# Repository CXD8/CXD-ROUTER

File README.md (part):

# CXD-ROUTER

CXD-ROUTER is a high-speed, modular router built on a Rockchip RK3588 SoC, powered by USB-C PD.

Goal of Project:
Most consumer routers are locked down and unupgrade. I built this as a high-performance router where networking hardware (e.g., m.2 Wi-Fi modules) can be easily upgraded using M.2 slots without replacing the entire device.

## Specifications and Features

| Component | Details |
| :--- | :--- |
| **SoC** | Rockchip RK3588 |
| **Memory** | Onboard LPDDR4 memory |
| **Storage** | Onboard eMMC storage |
| **Upgradable Modules** | M.2 slots for 2.5GbE Ethernet and BE3600 Wi-Fi cards |
| **Power** | USB-C Power Delivery (PD) 12V |
| **I/O** | Mini HDMI, USB-C, 2.5G RJ45 |

## Firmware, flashing and setup

1. Follow Firefly's or Fygo's existing documentation to flash the RK3588 board (image itself cant be uploaded here due to size; flashing tools included in firmware folder):  
   [Fygo ROC-RK3588-PC Upgrade Firmware Guide](https://help.fygonas.com/articles/v1/contact/arm-rk-usb)  
   [Firefly ROC-RK3588-PC Upgrade Firmware Guide](https://wiki.t-firefly.com/en/ROC-RK3588-PC/upgrade_firmware.html)  
3. Connect peripherals (OPT: M.2 WiFi Card)
4. Plug in your network cable and Mini HDMI to a monitor.
5. Connect a 12v USB-C PD compatible power source to the board.

## Images
 **PCB:**

 **Housing:**

## Bill of Materials
|CXD-ROUTER-V1.0.0.csv|                      |                           |                               | |   |                    |     |          |        |                               | | | |                                                                                                         |                                            |
|---------------------|---------------------------|--------------------------------|------------------------------------|------|--------|-------------------------|----------|---------------|--------------|-------------------------------------|-------|-------|-------|---------------------------------------------------------------------------------------------------------------|--------------------------------------------------|
|                     |                           |                                |                                    |      |        |                         |          |               |              |                                     |       |       |       |                                                                                                               |                                                  |
|                     |                           |                                |                                    |      |        |                         |          |               |              |                                     |       |       |       |                                                                                                               |                                                  |
|Uploaded data        |                           |                                |                                    |      |        |                         |          |               |              |                                     |       |       |       |                                                                                                               |                                                  |
|LCSC#                |Mrf#                       |Description                     |Package                             |Value |Quantity|Mfr.                     |Order Qty.|Unit Price(USD)|Ext.Price(USD)|Package                              |Min    |Mult   |SPQ    |Description                                                                                                    |Product Link                                      |
|C49062               |CL03A104KP3NNNC            |100nF X5R 10V 0201              |CL03A104KP3NNNC                     |      |46      |Samsung Electro-Mechanics|100       |0.0047         |0.47          |0201                                 |100    |100    |10000  |100nF �10% 10V Ceramic Capacitor X5R 0201                                                                      |https://www.lcsc.com/product-detail/C49062.html   |
|C59461               |CL10A226MQ8NRNC            |22uF X5R 6.3V 0603              |CL10A226MQ8NRNC                     |      |26      |Samsung Electro-Mechanics|40        |0.0313         |1.25          |0603                                 |20     |20     |4000   |22uF �20% 6.3V Ceramic Capacitor X5R 0603                                                                      |https://www.lcsc.com/product-detail/C59461.html   |
|C190187              |CC0201KRX5R5BB104          |100nF 6.3V 0201                 |RC0201FR-0749R9L                    |      |16      |YAGEO                    |100       |0.0040         |0.40          |0201                                 |100    |100    |15000  |100nF �10% 6.3V Ceramic Capacitor X5R 0201                                                                     |https://www.lcsc.com/product-detail/C190187.html  |
|C541330              |CC0201KRX5R5BB105          |1uF 6.3V 0201                   |RC0201FR-0749R9L                    |      |15      |YAGEO                    |100       |0.0071         |0.71          |0201                                 |100    |100    |15000  |1uF �10% 6.3V Ceramic Capacitor X5R 0201                                                                       |https://www.lcsc.com/product-detail/C541330.html  |
|C315248              |CL05A106MP5NUNC            |10uF X5R 4V 0402_BGA            |RC0402JR-070RL                      |      |13      |Samsung Electro-Mechanics|20        |0.0516         |1.03          |0402                                 |20     |20     |10000  |10uF �20% 10V Ceramic Capacitor X5R 0402                                                                       |https://www.lcsc.com/product-detail/C315248.html  |
|C3020456             |GRM188R60J226KEA0D         |22uF 0603 6.3V X5R              |GRM188R60J226KEA0D                  |      |12      |muRata                   |20        |0.0488         |0.98          |0603                                 |20     |20     |4000   |22uF �10% 6.3V Ceramic Capacitor X5R 0603                                                                      |https://www.lcsc.com/product-detail/C3020456.html |
|C307380              |CL03A104KO3NNNC            |100nF X5R 16V 0201              |RC0201FR-0749R9L                    |      |11      |Samsung Electro-Mechanics|100       |0.0062         |0.62          |0201                                 |100    |100    |10000  |100nF �10% 16V Ceramic Capacitor X5R 0201                                                                      |https://www.lcsc.com/product-detail/C307380.html  |
|C318688              |CL21A226KPCLRNC            |22uF 10V 0805 10%               |CL21A226KPCLRNC                     |      |11      |Samsung Electro-Mechanics|20        |0.0823         |1.65          |0805                                 |10     |10     |4000   |22uF �10% 10V Ceramic Capacitor X5R 0805                                                                       |https://www.lcsc.com/product-detail/C318688.html  |
|C190187              |CC0201KRX5R5BB104          |100nF 0201 6.3V                 |RC0201FR-0749R9L                    |      |10      |YAGEO                    |100       |0.0040         |0.40          |0201                                 |100    |100    |15000  |100nF �10% 6.3V Ceramic Capacitor X5R 0201                                                                     |https://www.lcsc.com/product-detail/C190187.html  |
|C105882              |CC0402KRX5R9BB104          |100nF 50V 0402                  |RC0402JR-070RL                      |      |10      |YAGEO                    |50        |0.0155         |0.78          |0402                                 |50     |50     |10000  |100nF �10% 50V Ceramic Capacitor X5R 0402                                                                      |https://www.lcsc.com/product-detail/C105882.html  |
|C14445               |CL05A105KP5NNNC            |1uF X5R 10V 0402                |FRC0402F1693TS                      |      |10      |Samsung Electro-Mechanics|50        |0.0128         |0.64          |0402                                 |50     |50     |10000  |1uF �10% 10V Ceramic Capacitor X5R 0402                                                                        |https://www.lcsc.com/product-detail/C14445.html   |
|C19702               |CL10A106KP8NNNC            |10uF X5R 10V 0603               |CL10A106KP8NNNC                     |      |9       |Samsung Electro-Mechanics|20        |0.0391         |0.78          |0603                                 |20     |20     |4000   |10uF �10% 10V Ceramic Capacitor X5R 0603                                                                       |https://www.lcsc.com/product-detail/C19702.html   |
|C107372              |CL05A105KQ5NNNC            |1uF X5R 6.3V 0201               |CL05A105KQ5NNNC                     |      |8       |Samsung Electro-Mechanics|100       |0.0076         |0.76          |0402                                 |100    |100    |10000  |1uF �10% 6.3V Ceramic Capacitor X5R 0402                                                                       |https://www.lcsc.com/product-detail/C107372.html  |
|C49062               |CL03A104KP3NNNC            |100nF X5R 100V 0201             |CL03A104KP3NNNC                     |      |8       |Samsung Electro-Mechanics|100       |0.0047         |0.47          |0201                                 |100    |100    |10000  |100nF �10% 10V Ceramic Capacitor X5R 0201                                                                      |https://www.lcsc.com/product-detail/C49062.html   |
|C3020456             |GRM188R60J226KEA0D         |22uF X5R 6.3V 0603              |GRM188R60J226KEA0D                  |      |8       |muRata                   |20        |0.0488         |0.98          |0603                                 |20     |20     |4000   |22uF �10% 6.3V Ceramic Capacitor X5R 0603                                                                      |https://www.lcsc.com/product-detail/C3020456.html |
|C440198              |GRM21BR61H106KE43L         |10uF 50V 0805                   |GRM21BR61H106KE43L                  |      |8       |muRata                   |10        |0.3246         |3.25          |0805                                 |5      |5      |3000   |10uF �10% 50V Ceramic Capacitor X5R 0805                                                                       |https://www.lcsc.com/product-detail/C440198.html  |
|C49062               |CL03A104KP3NNNC            |100nF 0201 10V X5R              |CL03A104KP3NNNC                     |      |7       |Samsung Electro-Mechanics|100       |0.0047         |0.47          |0201                                 |100    |100    |10000  |100nF �10% 10V Ceramic Capacitor X5R 0201                                                                      |https://www.lcsc.com/product-detail/C49062.html   |
|C170151              |CL05A225KO5NQNC            |16V 2.2uF 0402                  |FRC0402F1693TS                      |      |7       |Samsung Electro-Mechanics|50        |0.0291         |1.46          |0402                                 |50     |50     |10000  |2.2uF �10% 16V Ceramic Capacitor X5R 0402                                                                      |https://www.lcsc.com/product-detail/C170151.html  |
|C161455              |GRM033C80G105MEA2D         |1uF 4V 0201                     |RC0201FR-0749R9L                    |      |6       |muRata                   |20        |0.0279         |0.56          |0201                                 |20     |20     |15000  |1uF �20% 4V Ceramic Capacitor X6S 0201                                                                         |https://www.lcsc.com/product-detail/C161455.html  |
|C541330              |CC0201KRX5R5BB105          |1uF X5R 6.3V 0201               |RC0201FR-0749R9L                    |      |6       |YAGEO                    |100       |0.0071         |0.71          |0201                                 |100    |100    |15000  |1uF �10% 6.3V Ceramic Capacitor X5R 0201                                                                       |https://www.lcsc.com/product-detail/C541330.html  |
|C315248              |CL05A106MP5NUNC            |10V 10uF 0402                   |10uF_X5R_10V_0402                   |      |5       |Samsung Electro-Mechanics|20        |0.0516         |1.03          |0402                                 |20     |20     |10000  |10uF �20% 10V Ceramic Capacitor X5R 0402                                                                       |https://www.lcsc.com/product-detail/C315248.html  |
|C170151              |CL05A225KO5NQNC            |2.2uF X5R 6.3V 0402             |FRC0402F1693TS                      |      |5       |Samsung Electro-Mechanics|50        |0.0291         |1.46          |0402                                 |50     |50     |10000  |2.2uF �10% 16V Ceramic Capacitor X5R 0402                                                                      |https://www.lcsc.com/product-detail/C170151.html  |
|C14445               |CL05A105KP5NNNC            |1uF X5R 6.3V 0402               |FRC0402F1693TS                      |      |5       |Samsung Electro-Mechanics|50        |0.0128         |0.64          |0402                                 |50     |50     |10000  |1uF �10% 10V Ceramic Capacitor X5R 0402                                                                        |https://www.lcsc.com/product-detail/C14445.html   |
|C526941              |CC0201JRX7R8BB102          |1nF 25V X7R 0201                |RC0201FR-0749R9L                    |      |5       |YAGEO                    |100       |0.0052         |0.52          |0201                                 |100    |100    |15000  |1nF �5% 25V Ceramic Capacitor X7R 0201                                                                         |https://www.lcsc.com/product-detail/C526941.html  |
|C368809              |CL05A475KP5NRNC            |4.7uF 10V 04024                 |RC0402JR-070RL                      |      |4       |Samsung Electro-Mechanics|50        |0.0170         |0.85          |0402                                 |50     |50     |10000  |4.7uF �10% 10V Ceramic Capacitor X5R 0402                                                                      |https://www.lcsc.com/product-detail/C368809.html  |
|C190187              |CC0201KRX5R5BB104          |100nF 0201 6.3V X5R             |RC0201FR-0749R9L                    |      |4       |YAGEO                    |100       |0.0040         |0.40          |0201                                 |100    |100    |15000  |100nF �10% 6.3V Ceramic Capacitor X5R 0201                                                                     |https://www.lcsc.com/product-detail/C190187.html  |
|C3845593             |GRM158R61A226ME15D         |22uF X5R 10V                    |RC0402JR-070RL                      |      |4       |muRata                   |4         |0.7950         |3.18          |0402                                 |1      |1      |8000   |22uF �20% 10V Ceramic Capacitor X5R 0402                                                                       |https://www.lcsc.com/product-detail/C3845593.html |
|C105882              |CC0402KRX5R9BB104          |100nF 0402 50V                  |RC0402JR-070RL                      |      |4       |YAGEO                    |50        |0.0155         |0.78          |0402                                 |50     |50     |10000  |100nF �10% 50V Ceramic Capacitor X5R 0402                                                                      |https://www.lcsc.com/product-detail/C105882.html  |
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
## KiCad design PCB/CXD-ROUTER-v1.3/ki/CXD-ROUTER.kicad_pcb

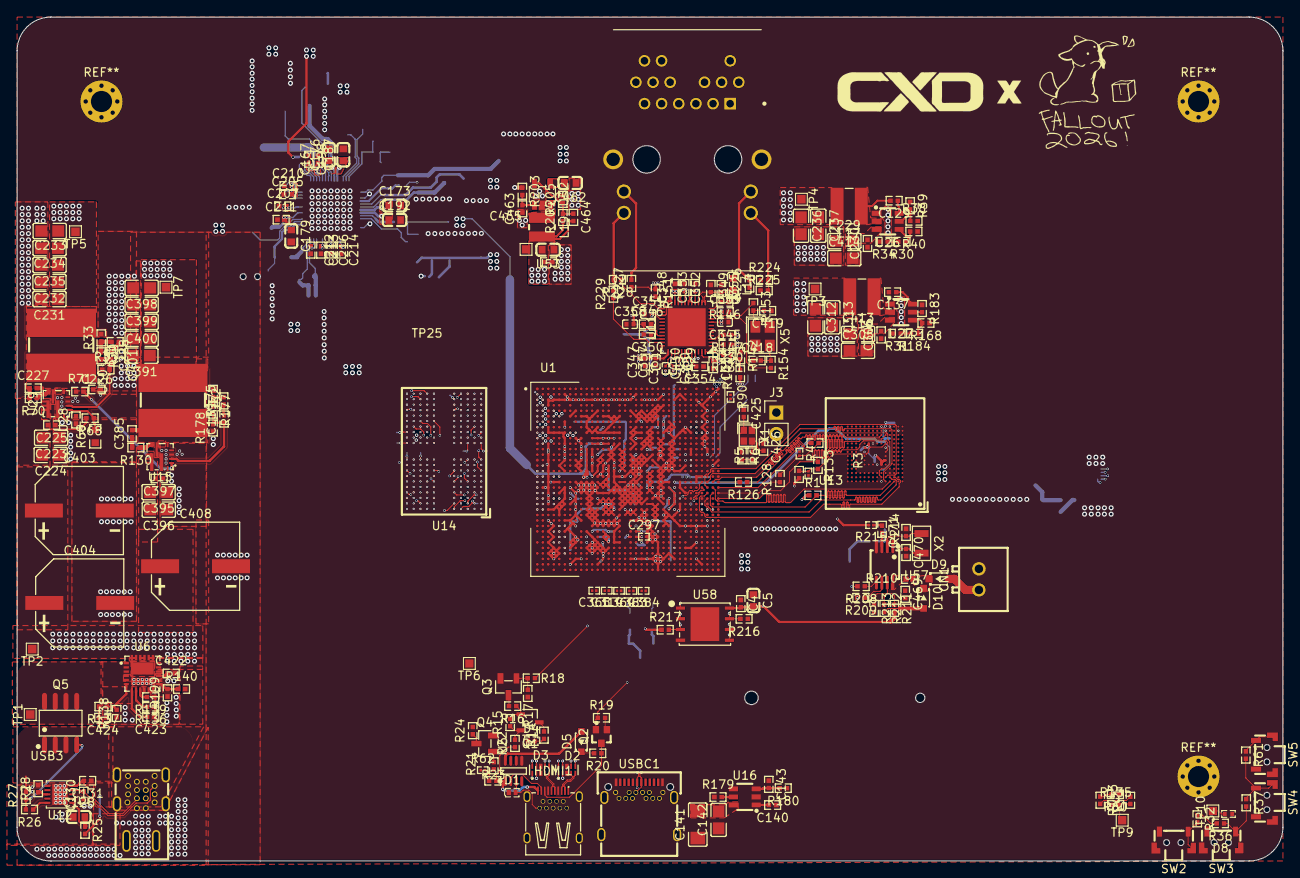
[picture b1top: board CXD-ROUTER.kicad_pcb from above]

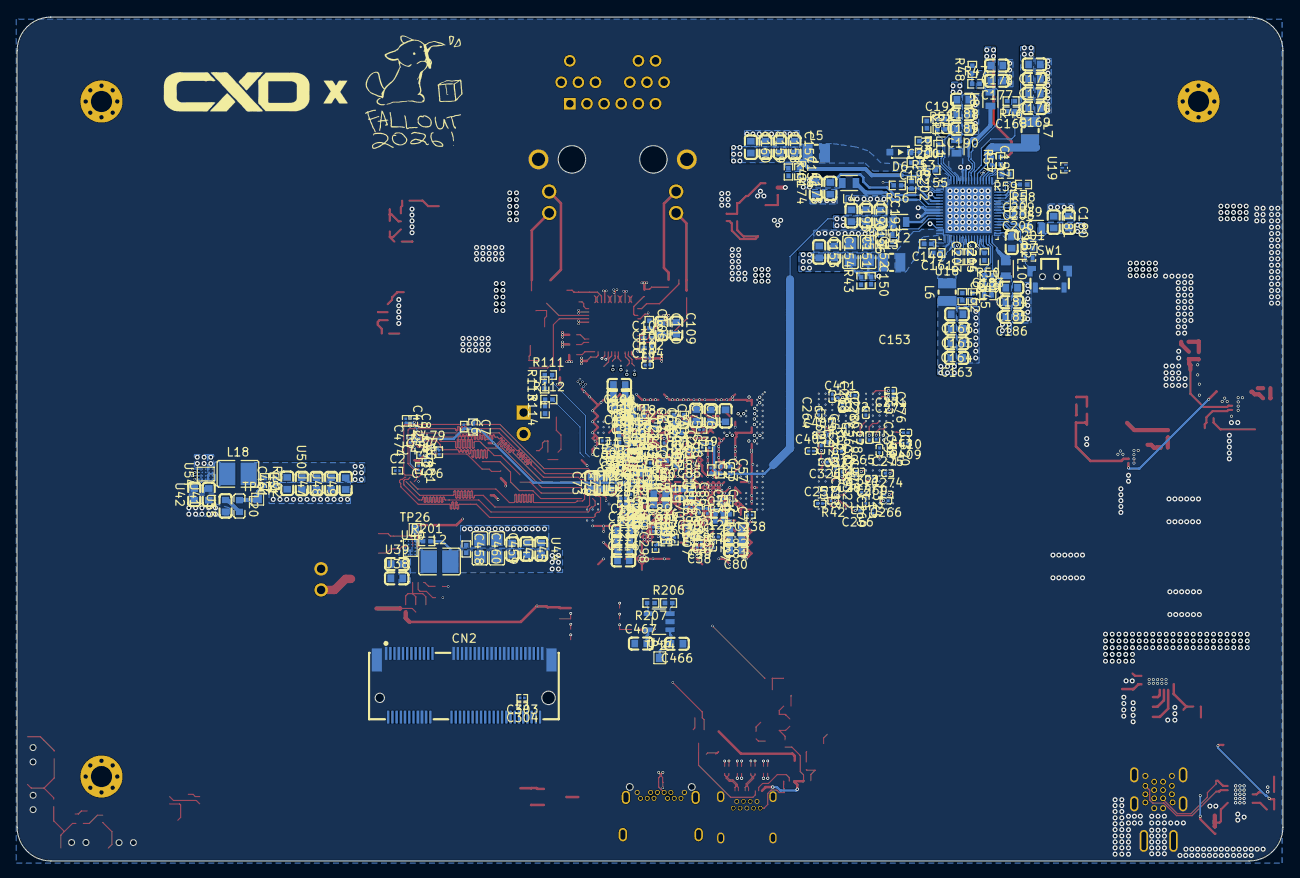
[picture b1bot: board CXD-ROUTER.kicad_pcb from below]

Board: 10 copper layers, 150.0 x 100.0 mm, 552 parts (301 on the bottom side), 311 nets.

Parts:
C1, C2, C3, C6, C8, C11, C12, C13, C14, C15, C17, C18, C20, C22, C24, C26, C28, C29, C30, C32, C33, C34, C35, C36, C37, C38, C39, C46, C47, C48, C49, C50, C51, C58, C63, C64, C70, C102, C112, C238, C281, C282, C286, C287, C288, C289, C290, C291, C292, C293, C295, C296, C297, C298, C303, C304, C307, C314, C364, C365, C383, C384, C439, C472, C474, C475, C476, C477, C478, C479, C481: -; RC0201FR-0749R9L
C4, C7, C19, C21, C23, C25, C27, C54, C55, C56, C65, C66, C67, C71, C72, C79, C87, C88, C96, C97, C98, C106, C107, C108, C113, C129, C130, C131, C137, C139, C140, C143, C149, C155, C161, C167, C225, C226, C227, C228, C230, C306, C349, C355, C385, C397, C424, C463, C465, C469: -; RC0402JR-070RL
C5, C128: -; CL10B105KA8NNNC
C16: -; RC0201FR-0747KL
C43, C150, C156, C162, C168, C183, C191, C196, C198, C199, C200, C201, C202, C203, C204, C205, C206, C207, C208, C209, C210, C211, C212, C213, C214, C215, C216, C346, C347, C348, C350, C352, C353, C354, C356, C359, C458, C461, C464: -; FRC0402F1693TS
C53, C59, C61, C62, C68, C69, C84, C85, C92, C93, C103, C104, C111, C121, C123, C125, C127, C256, C257, C260, C262, C263, C264, C265, C266, C267, C268, C269, C270, C271, C272, C273, C274, C275, C276, C277, C278, C280, C299, C300, C301, C302, C317, C318, C319, C320, C321, C322, C323, C324, C325, C326, C327, C360, C361, C405, C407, C409, C410, C411, C412, C429, C430: -; CL03A104KP3NNNC
C57, C345, C351, C357, C358: -; 10uF_X5R_10V_0402
C60, C86, C94, C95, C119, C120, C197: -; CL05A105KQ5NNNC
C73, C74, C75, C76, C77, C78, C80, C81, C82, C89, C90, C99, C100, C101, C109, C110, C114, C115, C116, C117: -; GRM188R60J226KEA0D
C141: -; GRM31CR61A107MEA8L
C142, C459, C460: -; GRM21BR61A476ME15L
C151, C152: -; CL21A476MQYNNNE
C153, C154, C157, C158, C159, C160, C163, C164, C165, C166, C169, C170, C171, C172, C174, C175, C177, C178, C180, C181, C185, C186, C188, C189, C193, C194: -; CL10A226MQ8NRNC
C173, C176, C179, C182, C184, C187, C190, C192, C195, C462, C466, C467: -; CL10A106KP8NNNC
C223, C224, C229, C305, C395, C396, C413, C414: -; GRM21BR61H106KE43L
C231, C232, C233, C234, C235, C236, C237, C312, C313, C391, C398, C399, C400, C401: -; CL21A226KPCLRNC
C239: -; RC0201FR-07240RL
C403, C404, C408: -; VKME1001K101MV
C418, C419, C422, C423, C425, C426, C470, C471: -; RC0402FR-071KL
CN1: -; B2B-XH-2_LF_SN
CN2: -; 2199230-4_C2977809
D1, D4: -; ESD5341N-2_TR
D2, D3: -; ESD5304D-10_TR
D5, D6, D9, D10: -; B5819WS_C916992
D7, D8: -; ESD5451N-2_TR
HDMI1: -; HDMI-GD-121PWB
J2: -; PULSE_JT4-1108HL
J3: -; PinHeader_1x02_P2.54mm_Vertical
L2, L18: -; FTC322512SR22MBCA
L3, L5, L6, L7: -; APS252012MR22F
L4, L8, L9, L10, L11, L12: -; MTC201208-R47MT
L14: -; BLM18PG330SN1D
L16, L17: -; FTC404030S3R3MGCA
L19: -; FTC303020D2R2MBCA
L20: -; BLM18KG121TN1D
Q1: -; WPM3407-3_TR
Q2: -; 2SK3018T106
Q3, Q4: -; S8050-J3Y_C18221467
Q5: -; AO4407A
R1, R2, R3, R15, R16, R18: -; RC0402JR-0710KL
R4, R62, R215: -; RC0201FR-0747KL
R5: -; CRCW040222R0JNED
R6: -; RC0402FR-07510KL
R14: -; RC0402JR-071KL
R17: -; RC0402JR-0720KL
R19, R40, R56, R57, R66, R178, R203, R207, R211, R216, R217: -; RC0402FR-0710KL
R20: -; RC0402JR-0727KL
R21, R22, R31, R33, R34, R47, R48, R70, R73, R126, R128, R130, R133, R135, R143, R153, R154, R176, R208, R209, R210, R212, R214, R224, R228, R229: -; RC0402JR-070RL
R23, R24, R111, R112: -; RC0402JR-07100KL
R25: -; RC0402FR-0710RL
R26: -; RC0402FR-075K1L
R27: -; RC0402FR-0749K9L
R28: -; 0402WGF1402TCE
R29: -; RC0402FR-0768KL
R30, R199: -; RC0402FR-0733K2L
R32, R201, R202: -; RC0402FR-07100RL
R35, R61: -; RC0402FR-0712KL
R36: -; RC0402FR-073KL
R37: -; RC0402FR-076K8L
R38: -; AF0402FR-07511KL
R39: -; ARG02BTC1053
R41, R43, R44, R45, R46, R49, R51, R55, R58, R59, R60, R71, R140, R168, R180, R183, R204: -; RC0402FR-07100KL
R42: -; RC0201FR-07240RL
R50, R175: -; RC0402FR-0720KL
R52, R113, R114, R138, R205: -; RC0402FR-07120KL
R53, R54: -; RT0402BRD07200KL
R68: -; FRC0402F1693TS
R69: -; RT0603BRD0736K1L
R90: -; RC0201FR-07200KL
R136: -; RC0402FR-07300RL
R137: -; RC0402FR-071ML
R139, R141: -; RC0402FR-071KL
R142: -; RC0402FR-0715KL
R146: -; RC0402FR-072K49L
R147, R151, R206, R230, R231: -; RC0402FR-074K7L
R177: -; RT0402BRD0745K3L
R179: -; AT0402BRD0726K1L
R184: -; RT0402BRD0723K7L
R213: -; RC0402JR-0722RL
R225, R226: -; CRCW0402249RFKED
R227: -; RC0402FR-07510RL
SW1, SW2, SW3, SW4, SW5: -; TS24CA
TP1, TP2, TP3, TP4, TP5, TP6, TP7, TP9, TP10, TP23, TP24, TP25, TP26: -; TestPoint_Pad_1.0x1.0mm
U1: -; BGA1088C65P34X34_2300X2300X204N
U5: -; RS0102YH8
U6: -; TPS259804ONRGER
U11: -; RTL8125BG-CG
U12: -; WDFN-10-1EP_3x3mm_P0.5mm_EP1.8x2.5mm
U13: -; KLMBG2JETD-B041
U14: -; H9HCNNN8KUMLHR-NME
U15: -; TPS56637RPAR
U16: -; TPS2553DBVR
U18: -; QFN35P700X700X90-69N
U19: -; RCLAMP0512TQTCT
U26, U27: -; TPS563201DDCR
U28: -; RT0402BRD0752K3L
U29: -; TPS56A37RPAR
U30, U32: -; FEXL0730A-3R3M
U38, U39, U41, U42, U43, U44, U45, U47, U48, U49, U50, U51, U53, U55: -; GRM188R60J226KEA0D
U40: -; RK860-2
U46: -; SGM2576YN5G_TR
U52: -; SY8089AAAC
U54: -; RK860-3
U57: -; HYM8563S
U58: -; W25Q256JWPIQ
USB3: -; HC-TYPE-C-16P-FL6_65Q-5A-06
USBC1: -; TYPE-C-31-M-04
X1: -; XL7EL89CKI-111YLC-24M
X2: -; SC-32S32_768kHz20PPM12_5pF
X5: -; XL2EL89COI-111YLC-25M

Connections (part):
0V95_ETH: C312.1, C313.1, C345.2, C347.2, C348.1, C351.2, C353.1, C356.1, C357.2, C359.1, L16.2, R31.2, TP3.1 (1_1), U11.8 (DVDD09), U11.11 (AVDD09), U11.16 (AVDD09), U11.22 (AVDD09), U11.28 (DVDD09), U11.37 (EVDD09), U11.47 (DVDD09)
3V3_M0: C391.1, C398.1, C399.1, C400.1, C401.1, CN2.2 (3.3V), CN2.4 (3.3V), CN2.72 (3.3V), CN2.74 (3.3V), R176.2, TP7.1 (1_1), U32.2
/5V_USB_1: C141.2, C142.2, U16.6 (OUT), USBC1.A4 (VBUS), USBC1.A9 (VBUS), USBC1.B4 (VBUS), USBC1.B9 (VBUS)
/15V_PD_OUT: C223.2, C224.2, C225.2, C229.2, C230.2, C395.2, C396.2, C397.2, C403.1, C404.1, C408.1, C414.2, R38.2, R68.2, R140.2, TP2.1 (1_1), U6.17 (OUT), U6.18 (OUT), U6.19 (OUT), U6.20 (OUT), U6.21 (OUT), U6.22 (OUT), U6.23 (OUT), U6.24 (OUT), U15.8 (VIN), U26.3 (VIN), U29.8 (VIN)
/15V_PD_OUT_UNFUSED: C424.2, Q5.5 (D), Q5.6 (D), Q5.7 (D), Q5.8 (D), R137.2, TP1.1 (1_1), U6.1 (IN), U6.2 (IN), U6.3 (IN), U6.16 (IN), U6.25 (IN)
/ETHERNET & MAGNETICS/AVDD33_PLL_E2: C349.2, C355.2, L14.2, U11.15 (AVDD33)
/ETHERNET & MAGNETICS/CKXTAL1_E2: R153.1, U11.10 (CKXTAL1)
/ETHERNET & MAGNETICS/CKXTAL2_E2: R154.2, U11.9 (CKXTAL2)
/ETHERNET & MAGNETICS/CLKREQB_E2: R231.2, U11.48 (CLKREQB)
/ETHERNET & MAGNETICS/DVDD33_29_E2: U11.29 (DVDD33), U11.46 (DVDD33)
/ETHERNET & MAGNETICS/EVDD33_E0: C354.2, J2.1 (TRCT2), J2.6 (TRCT3), J2.7 (TRCT1), J2.12 (TRCT4), U11.43 (EVDD33)
/ETHERNET & MAGNETICS/GIP/GPO_E2: R147.2, U11.3 (GPI)
/ETHERNET & MAGNETICS/LANWAKEB_E2: R230.2, U11.2 (LANWAKEB)
/ETHERNET & MAGNETICS/LED0/EEDI/SPISI/SDA_E2: R225.1, U11.30 (LED0/EEDI/SPISI/SDA)
/ETHERNET & MAGNETICS/LED1/EESK/SPISCK_E2: R151.2, R226.1, U11.27 (LED1/EESK/SPISC)
/ETHERNET & MAGNETICS/LED2/EEDO/SPISO_E2: R228.1, U11.25 (LED2/EEDO/SPIS0)
/ETHERNET & MAGNETICS/LED3_E2: R229.1, U11.35 (LED3)
/ETHERNET & MAGNETICS/MDIN0_2: J2.9 (TRD1-), U11.14 (MDIN0)
/ETHERNET & MAGNETICS/MDIN1_2: J2.3 (TRD2-), U11.18 (MDIN1)
/ETHERNET & MAGNETICS/MDIN2_2: J2.5 (TRD3-), U11.21 (MDIN2)
/ETHERNET & MAGNETICS/MDIN3_2: J2.11 (TRD4-), U11.24 (MDIN3)
/ETHERNET & MAGNETICS/MDIP0_2: J2.8 (TRD1+), U11.13 (MDIP0)
/ETHERNET & MAGNETICS/MDIP1_2: J2.2 (TRD2+), U11.17 (MDIP1)
/ETHERNET & MAGNETICS/MDIP2_2: J2.4 (TRD3+), U11.20 (MDIP2)
/ETHERNET & MAGNETICS/MDIP3_2: J2.10 (TRD4+), U11.23 (MDIP3)
/ETHERNET & MAGNETICS/RSET_E2: R146.2, U11.12 (RSET)
/HDMIIRX_DET_L: Q4.3 (C), R24.1
/HDMI_RXDDC_SCL_PORT: HDMI1.17 (SCL), U5.2 (B1)
/HDMI_RXDDC_SDA_PORT: D1.2, HDMI1.18 (SDA), U5.3 (B2)
/MIPI DSI & CSI INTERFACES - Q | R | P/PCIE30_0_REF: R90.1, U1.B34 (PCIE30_PORT0_RESREF)
/PMIC RK806-1/PMIC_FB6: C191.1, R51.2, R52.1, U18.31 (FB6)
/PMIC RK806-1/PMIC_FB9: C183.1, R49.2, R50.1, U18.66 (FB9)
/PMIC RK806-1/PMIC_SW1: L3.1, U18.50 (SW1_2), U18.51 (SW1_1)
/PMIC RK806-1/PMIC_SW2: L5.1, U18.35 (SW2), U18.36 (SW2)
/PMIC RK806-1/PMIC_SW3: L6.1, U18.55 (SW3)
/PMIC RK806-1/PMIC_SW4: L7.1, U18.23 (SW4)
/PMIC RK806-1/PMIC_SW5: L12.1, U18.45 (SW5)
/PMIC RK806-1/PMIC_SW6: L11.1, U18.29 (SW6)
/PMIC RK806-1/PMIC_SW9: L10.1, U18.68 (SW9)
/PMIC RK806-1/PMIC_SW10: L8.1, L9.1, U18.6 (SW8), U18.26 (SW10)
/PMIC RK806-1/PMIC_VDC: C200.1, R53.1, R54.1, U18.32 (VDC)
/PMU & CLOCK - E | F/XIN_24M: C425.2, R6.1, U1.R34 (XIN_24M), X1.1
/PMU & CLOCK - E | F/XOUT_24M: R5.1, R6.2, U1.T34 (XOUT_24M)
/TYPEC_VBUS: Q5.1 (S), Q5.2 (S), Q5.3 (S), R25.2, R27.2, USB3.A4 (VBUS), USB3.A9 (VBUS), USB3.B4 (VBUS), USB3.B9 (VBUS)
/VCCIO - J | K | I/VSEL4: R111.2, U1.T32 (PMIC_SLEEP4/GPIO0_C2_D)
/VCCIO - J | K | I/VSEL5: R112.2, U1.T30 (PMIC_SLEEP5/GPIO0_C3_D)
BIG/NPU_EN: U40.A2 (EN), U54.A2 (EN)
BOOT_SARADC_IN0: C314.2, R41.1, R135.2, TP9.1 (1_1), U1.AM16 (SARADC_IN0_BOOT)
CPU_BIG1_VSEL: U1.W28 (PMIC_SLEEP6/PDM0_SDI3_M1/GPIO0_D6_D), U54.A1 (VSEL)
DDR_CH0_A0_A: U1.T7 (DDR_CH0_A0_A), U14.H2 (CA0a)
DDR_CH0_A0_B: U1.M8 (DDR_CH0_A0_B), U14.R2 (CA0b)
DDR_CH0_A1_A: U1.T8 (DDR_CH0_A1_A), U14.J2 (CA1a)
DDR_CH0_A1_B: U1.M5 (DDR_CH0_A1_B), U14.P2 (CA1b)
DDR_CH0_A2_A: U1.P4 (DDR_CH0_A2_A), U14.H9 (CA2a)
DDR_CH0_A2_B: U1.N5 (DDR_CH0_A2_B), U14.R9 (CA2b)
DDR_CH0_A3_A: U1.P5 (DDR_CH0_A3_A), U14.H10 (CA3a)
DDR_CH0_A3_B: U1.N4 (DDR_CH0_A3_B), U14.R10 (CA3b)
DDR_CH0_A4_A: U1.R1 (DDR_CH0_A4_A), U14.H11 (CA4a)
DDR_CH0_A4_B: U1.K1 (DDR_CH0_A4_B), U14.R11 (CA4b)
DDR_CH0_A5_A: U1.P2 (DDR_CH0_A5_A), U14.J11 (CA5a)
DDR_CH0_A5_B: U1.L2 (DDR_CH0_A5_B), U14.P11 (CA5b)
DDR_CH0_CLKN_A: U1.N1 (DDR_CH0_CKB_A), U14.J9 (CK_ca)
DDR_CH0_CLKN_B: U1.M1 (DDR_CH0_CKB_B), U14.P9 (CK_cb)
DDR_CH0_CLKP_A: U1.N2 (DDR_CH0_CK_A), U14.J8 (CK_ta)
DDR_CH0_CLKP_B: U1.M2 (DDR_CH0_CK_B), U14.P8 (CK_tb)
DDR_CH0_DM0_A: U1.Y4 (DDR_CH0_DM0_A), U14.C3 (DMI0a)
DDR_CH0_DM0_B: U1.G4 (DDR_CH0_DM0_B), U14.Y3 (DMI0b)
DDR_CH0_DM1_A: U1.AB4 (DDR_CH0_DM1_A), U14.C10 (DMI1a)
DDR_CH0_DM1_B: U1.E4 (DDR_CH0_DM1_B), U14.Y10 (DMI1b)
DDR_CH0_DQ0_A: U1.U1 (DDR_CH0_DQ0_A), U14.B2 (DQ0a)
DDR_CH0_DQ0_B: U1.H1 (DDR_CH0_DQ0_B), U14.AA2 (DQ0b)
DDR_CH0_DQ1_A: U1.T2 (DDR_CH0_DQ1_A), U14.C2 (DQ1a)
DDR_CH0_DQ1_B: U1.J2 (DDR_CH0_DQ1_B), U14.Y2 (DQ1b)
DDR_CH0_DQ2_A: U1.T1 (DDR_CH0_DQ2_A), U14.E2 (DQ2a)
DDR_CH0_DQ2_B: U1.J1 (DDR_CH0_DQ2_B), U14.V2 (DQ2b)
DDR_CH0_DQ3_A: U1.R2 (DDR_CH0_DQ3_A), U14.F2 (DQ3a)
DDR_CH0_DQ3_B: U1.K2 (DDR_CH0_DQ3_B), U14.U2 (DQ3b)
DDR_CH0_DQ4_A: U1.W1 (DDR_CH0_DQ4_A), U14.F4 (DQ4a)
DDR_CH0_DQ4_B: U1.F1 (DDR_CH0_DQ4_B), U14.U4 (DQ4b)
DDR_CH0_DQ5_A: U1.V2 (DDR_CH0_DQ5_A), U14.E4 (DQ5a)
DDR_CH0_DQ5_B: U1.G2 (DDR_CH0_DQ5_B), U14.V4 (DQ5b)
DDR_CH0_DQ6_A: U1.V1 (DDR_CH0_DQ6_A), U14.C4 (DQ6a)
DDR_CH0_DQ6_B: U1.G1 (DDR_CH0_DQ6_B), U14.Y4 (DQ6b)
DDR_CH0_DQ7_A: U1.U2 (DDR_CH0_DQ7_A), U14.B4 (DQ7a)
DDR_CH0_DQ7_B: U1.H2 (DDR_CH0_DQ7_B), U14.AA4 (DQ7b)
DDR_CH0_DQ8_A: U1.AB2 (DDR_CH0_DQ8_A), U14.B11 (DQ8a)
DDR_CH0_DQ8_B: U1.D2 (DDR_CH0_DQ8_B), U14.AA11 (DQ8b)
DDR_CH0_DQ9_A: U1.AB1 (DDR_CH0_DQ9_A), U14.C11 (DQ9a)
DDR_CH0_DQ9_B: U1.C1 (DDR_CH0_DQ9_B), U14.Y11 (DQ9b)
DDR_CH0_DQ10_A: U1.AC1 (DDR_CH0_DQ10_A), U14.E11 (DQ10a)
DDR_CH0_DQ10_B: U1.C2 (DDR_CH0_DQ10_B), U14.V11 (DQ10b)
DDR_CH0_DQ11_A: U1.AC2 (DDR_CH0_DQ11_A), U14.F11 (DQ11a)
DDR_CH0_DQ11_B: U1.B1 (DDR_CH0_DQ11_B), U14.U11 (DQ11b)
DDR_CH0_DQ12_A: U1.Y1 (DDR_CH0_DQ12_A), U14.F9 (DQ12a)
DDR_CH0_DQ12_B: U1.F2 (DDR_CH0_DQ12_B), U14.U9 (DQ12b)
DDR_CH0_DQ13_A: U1.Y2 (DDR_CH0_DQ13_A), U14.E9 (DQ13a)
DDR_CH0_DQ13_B: U1.E1 (DDR_CH0_DQ13_B), U14.V9 (DQ13b)
DDR_CH0_DQ14_A: U1.AA1 (DDR_CH0_DQ14_A), U14.C9 (DQ14a)
DDR_CH0_DQ14_B: U1.E2 (DDR_CH0_DQ14_B), U14.Y9 (DQ14b)
DDR_CH0_DQ15_A: U1.AA2 (DDR_CH0_DQ15_A), U14.B9 (DQ15a)
DDR_CH0_DQ15_B: U1.D1 (DDR_CH0_DQ15_B), U14.AA9 (DQ15b)
DDR_CH0_DQS0_A_N: U1.U4 (DDR_CH0_DQS0N_A), U14.E3 (DQS0_ca)
DDR_CH0_DQS0_A_P: U1.U5 (DDR_CH0_DQS0P_A), U14.D3 (DQS0_ta)
DDR_CH0_DQS0_B_N: U1.J7 (DDR_CH0_DQS0N_B), U14.V3 (DQS0_cb)
DDR_CH0_DQS0_B_P: U1.J8 (DDR_CH0_DQS0P_B), U14.W3 (DQS0_tb)
DDR_CH0_DQS1_A_N: U1.AA4 (DDR_CH0_DQS1N_A), U14.E10 (DQS1_ca)
DDR_CH0_DQS1_A_P: U1.AA5 (DDR_CH0_DQS1P_A), U14.D10 (DQS1_ta)
DDR_CH0_DQS1_B_N: U1.F4 (DDR_CH0_DQS1N_B), U14.V10 (DQS1_cb)
DDR_CH0_DQS1_B_P: U1.F5 (DDR_CH0_DQS1P_B), U14.W10 (DQS1_tb)
DDR_CH0_LP4/4X_CS0_A: U1.R6 (DDR_CH0_LP4/4X_CS0_A), U14.H4 (CS0a)
DDR_CH0_LP4/4X_CS0_B: U1.L7 (DDR_CH0_LP4/4X_CS0_B), U14.R4 (CS0b)
DDR_CH1_LP4/4X_CKE0_C: U1.D16 (DDR_CH1_LP4/4X_CKE0/LP5_CS0_D), U1.E19 (DDR_CH1_LP4/4X_CS0_D)
DDR_CH1_LP4/4X_CKE1_C: U1.D19 (DDR_CH1_LP4/4X_CS1_D), U1.E16 (DDR_CH1_LP4/4X_CKE1/LP5_CS1_D)
DDR_RESET: C239.1, U1.T4 (DDR_CH0_RESET_A), U14.T11 (RESET)
FSPI_CLK: U1.AE33 (GMAC0_TXCLK/SDIO_CLK_M0/FSPI_CLK_M1/I2C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), U58.6 (CLK)
FSPI_CS0: U1.AB31 (GMAC0_PTP_REFCLK/FSPI_CS0N_M1/HDMI_TX1_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), U58.1 (CS#)
FSPI_D0: U1.AC32 (GMAC0_RXD2/SDIO_D0_M0/FSPI_D0_M1/UART6_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), U58.5 (DI(IO0))
FSPI_D1: U1.AC31 (GMAC0_RXD3/SDIO_D1_M0/FSPI_D1_M1/UART6_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), U58.2 (DO(IO1))
FSPI_D2: R217.2, U1.AE32 (GMAC0_RXCLK/SDIO_D2_M0/FSPI_D2_M1/I2C8_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), U58.3 (WP#(IO2))
FSPI_D3: R216.2, U1.AC33 (GMAC0_TXD2/SDIO_D3_M0/FSPI_D3_M1/I2C8_S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), U58.7 (HOLD#orRESET#(IO3))
GND: C1.1, C2.1, C3.2, C4.1, C5.1, C6.1, C7.1, C8.1, C11.2, C12.2, C13.1, C14.2, C15.2, C16.2, C17.2, C18.2, C19.2, C20.2, C21.2, C22.2, C23.2, C24.2, C25.2, C26.2, C27.2, C28.2, C29.2, C30.2, C32.1, C33.1, C34.1, C35.1, C36.1, C37.1, C38.1, C39.1, C43.1, C46.2, C47.2, C48.2, C49.2, C50.2, C51.2, C53.1, C54.1, C55.1, C56.1, C57.1, C58.1, C59.1, C60.2, C61.2, C62.2, C63.2, C64.2, C65.2, C66.2, C67.2, C68.1, C69.1, C70.1, C71.1, C72.1, C73.1, C74.2, C75.2, C76.2, C77.1, C78.1, C79.1, C80.1, C81.1, C82.1, C84.1, C85.1, C86.2, C87.2, C88.2, C89.2, C90.2, C92.2, C93.2, C94.1, C95.1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
HDMIIRX_HPDOUT_H: R18.2, U1.AA27 (HDMI_TX0_HPD_M1/PCIE30X2_PERSTN_M2/HDMI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)
HDMI_RX_CEC: Q2.1 (S), R19.1, U1.AG23 (CIF_D13/PCIE20X1_2_PERSTN_M0/HDMI_RX_CE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)
HDMI_RX_CEC_PORT: HDMI1.15 (CEC), Q2.3 (D), R20.1
HDMI_RX_CLK_PORT_N: D3.1, D3.10, HDMI1.14 (TMDS_CLOCK-), U1.AF5 (HDMI_RX_CLKN)
HDMI_RX_CLK_PORT_P: D3.2, D3.9, HDMI1.12 (TMDS_CLOCK+), U1.AF6 (HDMI_RX_CLKP)
HDMI_RX_D0_PORT_N: D3.4, D3.7, HDMI1.11 (TMDS_DATA0-), U1.AG4 (HDMI_RX_D0N)
HDMI_RX_D0_PORT_P: D3.5, D3.6, HDMI1.9 (TMDS_DATA0+), U1.AG5 (HDMI_RX_D0P)
HDMI_RX_D1_PORT_N: D2.1, D2.10, HDMI1.8 (TMDS_DATA1-), U1.AH5 (HDMI_RX_D1N)
HDMI_RX_D1_PORT_P: D2.2, D2.9, HDMI1.6 (TMDS_DATA1+), U1.AH6 (HDMI_RX_D1P)
HDMI_RX_D2_PORT_N: D2.4, D2.7, HDMI1.5 (TMDS_DATA2-), U1.AJ4 (HDMI_RX_D2N)
HDMI_RX_D2_PORT_P: D2.5, D2.6, HDMI1.3 (TMDS_DATA2+), U1.AJ5 (HDMI_RX_D2P)
I2C0_SCL_M2: U1.W30 (I2S1_SDO0_M1/CPU_BIG0_AVS/I2C0_SCL_M2/U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), U54.A3 (SCL)
I2C0_SDA_M2: U1.W29 (I2S1_SDO1_M1/I2C0_SDA_M2/UART1_RX_M2/HD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), U54.B1 (SDA)
I2C1_SDA_M2: U1.V28 (I2S1_SDO3_M1/CPU_BIG1_AVS/I2C1_SDA_M2/C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), U40.B1 (SDA)
I2C6_SCL_M0: R209.2, U1.W31 (I2S1_SDI3_M1/PDM0_SDI1_M1/I2C6_SCL_M0/U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)
I2C6_SDA_M0: R208.2, U1.V31 (I2S1_SDI2_M1/PDM0_SDI0_M1/I2C6_SDA_M0/U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)
NPU_VSEL: U1.U32 (PMIC_SLEEP3/GPIO0_C1_D), U40.A1 (VSEL)
unnamed: C139.2, R175.1
unnamed: C227.1, R70.2
unnamed: C228.1, R73.1
unnamed: C385.1, R130.2
unnamed: C418.2, R154.1, X5.3
unnamed: C419.2, R153.2, X5.1
unnamed: C426.2, R5.2, X1.3
unnamed: CN1.1 (POS), D9.2 (A)
unnamed: C304.2, CN2.37 (TX-N)
unnamed: C303.2, CN2.35 (TX-P)
unnamed: D4.2, R14.1
unnamed: D5.1 (K), R20.2
unnamed: C199.1, D6.1 (K), R53.2
unnamed: J2.17 (LEDG1+), R224.2, R225.2
unnamed: J2.16 (LEDG1-), R226.2
unnamed: J2.19 (LEDY+), R228.2, R229.2
unnamed: J2.18 (LEDY-), R227.2
unnamed: L2.1, U40.D3 (LX), U40.D4 (LX), U40.E3 (LX), U40.E4 (LX)
unnamed: L18.1, U54.D3 (LX), U54.D4 (LX), U54.E3 (LX), U54.E4 (LX)
unnamed: Q1.3 (D), R14.2
unnamed: Q1.1 (G), R15.2, R16.1
unnamed: Q1.2 (S), R15.1, R22.2
unnamed: Q3.1 (B), R17.1, R18.1
unnamed: Q3.3 (C), R16.2
unnamed: Q4.1 (B), R21.2
unnamed: Q5.4 (G), R26.2, R27.1
unnamed: R21.1, R23.1, R62.2
unnamed: R29.1, R33.1, R73.2
unnamed: R30.2, R34.1
unnamed: R32.2, SW2.1, SW2.4
unnamed: R36.1, R37.2, SW3.1, SW3.4
unnamed: R37.1, R61.2, SW4.1, SW4.4
unnamed: R61.1, SW5.1, SW5.4
unnamed: R175.2, R176.1, R177.1
unnamed: R31.1, R184.2
unnamed: R126.2, U1.V34 (EMMC_CLKOUT/GPIO2_A1_D)
unnamed: R128.2, U1.Y34 (EMMC_DATA_STROBE/I2C2_SDA_M2/UART5_CTSN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)
unnamed: R133.2, U1.AA34 (EMMC_RSTN/I2C2_SCL_M2/UART5_RTSN_M1/GPI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)
unnamed: C16.1, U1.AF19 (MIPI_D/C_PHY1_VREG)
unnamed: R137.1, R138.2, U6.6 (EN/UVLO)
unnamed: R136.2, U6.8 (ILIM)
unnamed: R139.2, U6.9 (IMON)
unnamed: C423.2, U6.7 (ITIMER)
unnamed: R140.1, R199.2, U6.13 (PG)
unnamed: C422.1, U6.15 (dVdt)
unnamed: R141.2, R142.2, U11.1 (ISOLATEB)
unnamed: C130.2, U12.4 (CC1), USB3.A5 (CC1)
unnamed: C131.2, U12.5 (CC2), USB3.B5 (CC2)
unnamed: R26.1, U12.10 (GATE)
unnamed: C128.2, R25.1, U12.1 (VIN)
unnamed: R28.1, U12.8 (VSET)
unnamed: C2.2, U13.C2 (VDDI)
unnamed: R66.1, U14.T2 (ODTb)
unnamed: R42.1, U14.A5 (ZQ0)
unnamed: R130.1, U15.7 (BOOT)
unnamed: C139.1, R177.2, R178.2, U15.2 (FB)
unnamed: C385.2, U15.6 (SW), U32.1
unnamed: C143.2, R180.2 (2_2), U16.3 (EN), U16.4 (/FAULT)
unnamed: R179.2, U16.5 (ILIM)
unnamed: L4.1, U18.42 (SW7)
unnamed: R38.1, R39.2, U26.5 (EN)
unnamed: C129.2, L17.1, U26.2 (SW)
unnamed: C129.1, U26.6 (VBST)
unnamed: R30.1, R40.2, U26.4 (VFB)
unnamed: C137.2, L16.1, U27.2 (SW)
unnamed: C137.1, U27.6 (VBST)
unnamed: R168.2, R184.1, U27.4 (VFB)
unnamed: R70.1, U29.7 (BOOT)
unnamed: R68.1, R69.2, U29.1 (EN)
unnamed: C228.2, R29.2, R35.2, U29.2 (FB)
unnamed: U28.2, U29.10 (MODE)
unnamed: R71.1, U29.4 (PG)
unnamed: C226.1, U29.5 (SS)
unnamed: C227.2, U29.6 (SW), U30.1
unnamed: R207.2, U46.4 (EN)
unnamed: R206.2, U46.3 (ILIM/OCB)
unnamed: C463.2, R203.2, U52.1 (EN)
unnamed: C464.1, R204.2, R205.1, U52.5 (FB)
unnamed: L19.1, U52.3 (LX)
unnamed: R211.1, R212.1, R213.1, U57.7 (CLKOUT)
unnamed: R214.2, U57.3 (INT#)
unnamed: C470.1, U57.1 (OSCI), X2.2
unnamed: C471.1, U57.2 (OSCO), X2.1
unnamed: R209.1, U57.6 (SCL)
unnamed: R208.1, U57.5 (SDA)
unnamed: C469.1, R210.1, U57.8 (VDD)
PCIE20_1_2_WAKEn_M1_L: U1.AG24 (CIF_D15/PCIE30X2_WAKEN_M2/HDMI_RX_SDA_M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), U1.AH24 (CIF_D12/PCIE20X1_2_WAKEN_M0/HDMI_TX0_SD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)
PCIE20_2_REFCLKN: U1.G30 (PCIE20_2_REFCLKN), U11.45 (REFCLK_N)
PCIE20_2_REFCLKP: U1.G31 (PCIE20_2_REFCLKP), U11.44 (REFCLK_P)
PCIE20_2_RXN: C360.1, C360.2, U1.J30 (PCIE20_2_RXN/SATA30_2_RXN/USB30_2_SSRXN), U11.39 (HSON)
PCIE20_2_RXP: C361.1, C361.2, U1.J31 (PCIE20_2_RXP/SATA30_2_RXP/USB30_2_SSRXP), U11.38 (HSOP)
PCIE20_2_TXN: C430.1, C430.2, U1.H29 (PCIE20_2_TXN/SATA30_2_TXN/USB30_2_SSTXN), U11.42 (HSIN)
PCIE20_2_TXP: C429.1, C429.2, U1.H30 (PCIE20_2_TXP/SATA30_2_TXP/USB30_2_SSTXP), U11.41 (HSIP)
PCIE30_PORT0_RX0N: CN2.43 (RX-N), U1.G34 (PCIE30_PORT0_RX0N)
PCIE30_PORT0_RX0P: CN2.41 (RX-P), U1.G33 (PCIE30_PORT0_RX0P)
PCIE30_PORT0_TX0N: C304.1, U1.D33 (PCIE30_PORT0_TX0N)
PCIE30_PORT0_TX0P: C303.1, U1.D32 (PCIE30_PORT0_TX0P)
PCIE30x1_0_CLKREQn_M1_L: CN2.53 (CLKREQ0), U1.AL29 (CIF_D3/BT1120_D3/PCIE30X1_0_CLKREQN_M1/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)
PCIE30x1_0_PERSTn_M1_L: CN2.52 (PERSTO), U1.AK27 (CIF_D5/BT1120_D5/I2S1_SDI0_M0/PCIE30X1_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)
PCIE30x1_0_WAKEn_M1_L: CN2.55 (PEWAKE0), U1.AL28 (CIF_D4/BT1120_D4/PCIE30X1_0_WAKEN_M1/I2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)
PCIE30x2_PERSTn_M1_L: U1.AK26 (CIF_CLKIN/BT1120_CLKOUT/I2S1_SDI3_M0/PC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), U11.36 (PERSTB)
PMIC_EXT_EN_OUT: R203.1, U18.39 (EXT_EN)
PMIC_INT_L: R57.1, U1.M30 (PMIC_INT_L/GPIO0_A7_U), U18.19 (INT)
PMIC_PWR_CTRL2: R112.1, R114.2, U18.61 (PWRCRTL2)
PMIC_PWR_CTRL3: R111.1, R113.2, U18.16 (MISO/PWRCRTL3)
PMIC_SPI_CS: R59.2, U1.K29 (CLK32K_IN/CLK32K_OUT0/GPIO0_B2__U), U1.K30 (SPI2_CS0_M2/I2C1_SDA_M1/PWM5_M0/UART0_T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), U18.18 (CS)
PMIC_SPI_MOSI: R58.2, U1.L29 (SPI2_MISO_M2/I2C0_SCL_M0/GPIO0_B3_Z), U18.15 (MOSI/SDA)
POW_EXT_SWR: R183.2, U27.5 (EN)
PWRON_L: C201.1, D7.1 (C), SW1.4, U18.4 (PWRON)
RESET_L: C202.2, R56.1, U1.M31 (NPOR), U18.40 (RESETB)
RTC_INT_L: R214.1, R215.1, U1.L30 (SPI2_CS1_M2/I2C1_SCL_M1/UART0_RX_M1/GPI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)
SARADC_IN4_EXP: C384.2, U1.AM17 (SARADC_IN4)
SARADC_VIN1_KEY/RECOVERY: C364.2, D8.2 (A), R32.1, R36.2, TP10.1 (1_1), U1.AL16 (SARADC_IN1)
SARADC_VIN2_LCD_ID: C365.2, U1.AK16 (SARADC_IN2)
SARADC_VIN3_HP_HOOK: C383.2, U1.AN17 (SARADC_IN3)
SARADC_VIN5_EVB_HW_ID: R60.2, R143.1, U1.AK15 (SARADC_IN5)
TYPEC1_SSRX1N: U1.AP8 (TYPEC1_SSRX1N/DP1_TX0N), USBC1.B10 (SSRXn1)
TYPEC1_SSRX1P: U1.AN8 (TYPEC1_SSRX1P/DP1_TX0P), USBC1.B11 (SSRXp1)
TYPEC1_SSTX1N: U1.AN9 (TYPEC1_SSTX1N/DP1_TX1N), USBC1.A3 (SSTXn1)
TYPEC1_SSTX1P: U1.AP9 (TYPEC1_SSTX1P/DP1_TX1P), USBC1.A2 (SSTXP1)
TYPEC1_SSTX2N: U1.AN11 (TYPEC1_SSTX2N/DP1_TX3N), USBC1.B3 (SSTXn2)
TYPEC1_SSTX2P: U1.AP11 (TYPEC1_SSTX2P/DP1_TX3P), USBC1.B2 (SSTXp2)
TYPEC1_USB20_OTG_D_N: U1.AL6 (USB20_HOST0_DM), USBC1.A7 (DN1), USBC1.B7 (DN2)
TYPEC1_USB20_OTG_D_P: U1.AK6 (USB20_HOST0_DP), USBC1.A6 (DP1), USBC1.B6 (DP2)
U29_PG: R71.2, U15.1 (EN)
UART2_RX_M0: J3.2, U1.R29 (I2S1_SCLK_M1/JTAG_TMS_M2/I2C1_SDA_M0/UA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)
UART2_TX_M0: J3.1, U1.P29 (I2S1_MCLK_M1/JTAG_TCK_M2/I2C1_SCL_M0/UA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)
VCC1V8_PMU_DDR_S3: C46.1, C301.1, R47.1, R48.1, R215.2, U1.N28 (PMUIO1_1V8), U1.R27 (PMUIO2_1V8), U14.F1 (VDD1), U14.F12 (VDD1), U14.G4 (VDD1), U14.G9 (VDD1), U14.T4 (VDD1), U14.T9 (VDD1), U14.U1 (VDD1), U14.U12 (VDD1)
VCC3V3_ETH: C236.1, C237.1, C346.1, C350.1, C352.1, C358.2, L14.1, L17.2, R34.2, R141.1, R147.1, R151.1, R224.1, R227.1, R230.1, R231.1, TP4.1 (1_1), U11.19 (AVDD33), U11.33 (AVDD33), U11.34 (AVDD33_XTAL)
VCC4V0_SYS: C198.2, C199.2, C204.2, C462.2, U18.21 (VCCA), U18.64 (VCC12), U19.1, U19.2, U38.2, U39.2, U40.D1 (VIN), U40.D2 (VIN), U40.E1 (VIN), U40.E2 (VIN), U41.2, U42.2, U52.4 (IN), U54.D1 (VIN), U54.D2 (VIN), U54.E1 (VIN), U54.E2 (VIN)
VCC5V0_SYS: C140.2, C149.1, C155.1, C161.1, C167.1, C173.1, C176.1, C179.1, C182.1, C187.1, C192.1, C231.1, C232.1, C233.1, C234.1, C235.1, C305.2, C306.2, C413.2, R33.2, TP5.1 (1_1), U16.1 (IN), U18.1 (VCC9), U18.7 (VCC8), U18.22 (VCC4), U18.27 (VCC10), U18.28 (VCC6), U18.33 (VCC2_2), U18.34 (VCC2_1), U18.52 (VCC1_1), U18.53 (VCC1_2), U18.54 (VCC3), U27.3 (VIN), U30.2
VCC5V_HDMIRX_PORT: HDMI1.19 (+5V), R22.1, R23.2, U5.1 (VCCB)
VCCA_1V8_S0: C18.1, C19.1, C22.1, C23.1, C26.1, C29.1, C34.2, C35.2, C38.2, C39.2, C49.1, C50.1, C51.1, C216.1, C307.1, R41.2, R143.2, U1.AG11 (USB20_AVDD_1V8), U1.AG14 (TYPEC0_DP0_VDDH_1V8), U1.AH18 (SARADC_AVDD_1V8), U1.AJ13 (TYPEC1_DP1_VDDA_0V85), U1.G23 (PCIE30_PORT0_AVDD1V8), U1.H23 (PCIE30_PORT1_AVDD1V8), U1.K16 (DDR_CH1_PLL_AVDD1V8), U1.K27 (PCIE20_SATA30_USB30_2_AVDD_1V8), U1.L27 (PCIE20_SATA30_1_AVDD_1V8), U1.M12 (DDR_CH0_PLL_AVDD1V8), U1.M27 (PCIE20_SATA30_0_AVDD_1V8), U1.N27 (OSC_1V8), U1.U18 (PLL_AVDD1V8), U18.60 (PLDO1)
VCCA_3V3_S0: C127.1, C213.1, U1.AE4 (HDMI_RX_VPH3V3), U1.AE5 (HDMI_RX_DVDD3V3), U1.AJ10 (USB20_AVDD_3V3), U18.63 (PLDO4)
VCCIO_SD_S0: C12.1, C212.1, U1.Y7 (VCCIO2), U18.65 (PLDO5)
VCC_1V1_NLDO_S3: C205.2, C206.2, C464.2, C465.2, L19.2, R204.1, TP25.1 (1_1), U18.9 (VCC14), U18.13 (VCC13), U53.2
VCC_1V8_S0: C13.2, C15.1, C215.1, C286.2, C287.2, C289.2, C293.2, C298.2, C299.1, Q2.2 (G), R19.2, R24.2, R207.1, U1.AA7 (VCCIO2_1V8), U1.AA26 (MIPI_CSI1_AVCC1V8), U1.AB26 (MIPI_CSI0_AVCC1V8), U1.AC25 (VCCIO6_1V8), U1.AJ19 (MIPI_D/C_PHY1_VDD_1V8), U1.AJ20 (MIPI_D/C_PHY0_VDD_1V8), U1.G20 (VCCIO1_1V8), U1.H20 (VCCIO4_1V8), U1.H21 (VCCIO4), U1.W25 (VCCIO5_1V8), U1.Y26 (VCCIO3_1V8), U18.58 (PLDO2)
VCC_1V8_S3: C4.2, C5.2, C6.2, C7.2, C8.2, C11.1, C177.2, C178.2, C472.2, C474.2, C475.2, C481.2, L8.2, R1.1, R2.1, R3.1, R47.2, R56.2, R57.2, R211.2, R216.1, R217.1, U1.V26 (EMMCIO_1V8), U13.C6 (VDD), U13.M4 (VDD), U13.N4 (VDD), U13.P3 (VDD), U13.P5 (VDD), U18.25 (VOUT10), U58.8 (VCC)
VCC_1V8_S3_PLDO6: C197.2, R48.2, U18.20 (VCCIO)
VCC_2V0_PLDO_S3: C174.2, C175.2, C203.2, L4.2, U18.41 (VOUT7), U18.59 (VCC11)
VCC_3V3_S0: C288.2, C300.1, C466.2, D5.2 (A), TP24.1 (1_1), U1.AC26 (VCCIO6), U1.W26 (VCCIO5), U5.4 (OE), U5.8 (VCCA), U46.1 (VOUT)
VCC_3V3_S3: C180.2, C181.2, C302.1, C467.2, C476.2, C477.2, C478.2, C479.2, D10.2 (A), L9.2, R212.2, U1.P28 (PMUIO2), U13.E6 (VDDF), U13.F5 (VDDF), U13.J10 (VDDF), U13.K9 (VDDF), U18.5 (VOUT8), U46.5 (VIN)
VCC_RTC: D9.1 (K), D10.1 (K), R210.2
VDD2_DDR_S3: C188.2, C189.2, C190.2, C191.2, C257.2, C260.2, C263.2, C265.2, C267.2, C269.2, C271.2, C273.2, C275.2, C317.2, C320.2, C323.2, C325.2, C326.2, C327.2, C405.2, C407.2, C409.2, C410.2, C411.2, C412.2, L11.2, R52.2, R66.2, U14.A4 (VDD2), U14.A9 (VDD2), U14.AB4 (VDD2), U14.AB9 (VDD2), U14.F5 (VDD2), U14.F8 (VDD2), U14.H1 (VDD2), U14.H5 (VDD2), U14.H8 (VDD2), U14.H12 (VDD2), U14.K1 (VDD2), U14.K3 (VDD2), U14.K10 (VDD2), U14.K12 (VDD2), U14.N1 (VDD2), U14.N3 (VDD2), U14.N10 (VDD2), U14.N12 (VDD2), U14.R1 (VDD2), U14.R5 (VDD2), U14.R8 (VDD2), U14.R12 (VDD2), U14.U5 (VDD2), U14.U8 (VDD2), U18.30 (VOUT6)
VDDA_0V75_S0: C125.1, C208.2, U1.AE8 (HDMI_RX_AVDD0V75), U1.AH10 (USB20_DVDD_0V75), U18.11 (NLDO3)
VDDA_0V85_S0: C27.1, C28.1, C30.1, C32.2, C33.2, C36.2, C37.2, C207.2, U1.AG13 (TYPEC1_DP1_VDDH_1V8), U1.AH13 (TYPEC1_DP1_VDD_0V85), U1.AH14 (TYPEC0_DP0_VDDA_0V85), U1.AJ14 (TYPEC0_DP0_VDD_0V85), U1.K28 (PCIE20_SATA30_USB30_2_AVDD_0V85), U1.L28 (PCIE20_SATA30_1_AVDD_0V85), U1.M28 (PCIE20_SATA30_0_AVDD_0V85), U18.10 (NLDO4)
VDDA_1V2_S0: C17.1, C214.1, C297.2, U1.AH19 (MIPI_D/C_PHY1_VDD_1V2), U1.AH20 (MIPI_D/C_PHY0_VDD_1V2), U18.57 (PLDO3)
VDDA_DDR_PLL_S0: C209.2, C282.2, U1.L15 (DDR_CH1_PLL_DVDD), U1.N12 (DDR_CH0_PLL_DVDD), U18.12 (NLDO2)
VDDQ_DDR: C256.2, C262.2, C264.2, C266.2, C268.2, C270.2, C272.2, C274.2, C276.2, C277.2, C278.2, C280.2, C318.2, C319.2, C321.2, C322.2, C324.2, R42.2, U14.AA3 (VDDQ), U14.AA5 (VDDQ), U14.AA8 (VDDQ), U14.AA10 (VDDQ), U14.B3 (VDDQ), U14.B5 (VDDQ), U14.B8 (VDDQ), U14.B10 (VDDQ), U14.D1 (VDDQ), U14.D5 (VDDQ), U14.D8 (VDDQ), U14.D12 (VDDQ), U14.F3 (VDDQ), U14.F10 (VDDQ), U14.U3 (VDDQ), U14.U10 (VDDQ), U14.W1 (VDDQ), U14.W5 (VDDQ), U14.W8 (VDDQ), U14.W12 (VDDQ)
VDDQ_DDR_CKE_S3: C439.2, U1.H13 (DDR_CH1_VDDQ_CKE), U1.N8 (DDR_CH0_VDDQ_CKE)
VDDQ_DDR_S0: C183.2, C184.2, C185.2, C186.2, L10.2, R50.2, U1.K11 (DDR_CH1_VDDQ_0), U1.K12 (DDR_CH1_VDDQ_1), U1.K13 (DDR_CH1_VDDQ_2), U1.K14 (DDR_CH1_VDDQ_3), U1.K15 (DDR_CH1_VDDQ_4), U1.M10 (DDR_CH0_VDDQ_0), U1.N10 (DDR_CH0_VDDQ_1), U1.P10 (DDR_CH0_VDDQ_2), U1.R10 (DDR_CH0_VDDQ_3), U1.T10 (DDR_CH0_VDDQ_4), U18.67 (VOUT9)
VDD_0V75_S0: C14.1, C20.1, C21.1, C24.1, C25.1, C211.2, C238.1, C290.2, C291.2, C292.2, C295.2, C296.2, U1.AA25 (MIPI_CSI1_AVCC0V75), U1.AB25 (MIPI_CSI0_AVCC0V75), U1.AD3 (OTP_VDDOTP_0V75), U1.AG19 (MIPI_D/C_PHY1_VDD), U1.AG20 (MIPI_D/C_PHY0_VDD), U1.G24 (PCIE30_PORT0_AVDD0V75), U1.H24 (PCIE30_PORT1_AVDD0V75), U1.V20 (PLL_DVDD0V75), U18.8 (NLDO5)
VDD_0V75_S3: C47.1, C48.1, C210.2, U1.P27 (PMU_0V75), U18.14 (NLDO1)
VDD_CPU_BIG1_MEM_S0: C59.2, C60.1, C119.1, C123.2, L20.2, U1.M19 (VDD_CPU_BIG0_MEM_0), U1.M21 (VDD_CPU_BIG1_MEM_0), U1.N19 (VDD_CPU_BIG0_MEM_1), U1.N21 (VDD_CPU_BIG1_MEM_1), U55.2
VDD_CPU_BIG1_S0: C61.1, C62.1, C63.1, C64.1, C65.1, C66.1, C67.1, C74.1, C75.1, C76.1, C92.1, C93.1, C94.2, C95.2, C96.2, C97.2, C98.2, C99.1, C100.1, C101.1, C461.2, L18.2, L20.1, R202.1, R202.2, TP23.1 (1_1), U1.K23 (VDD_CPU_BIG1_9), U1.K24 (VDD_CPU_BIG1_0), U1.L23 (VDD_CPU_BIG1_8), U1.L24 (VDD_CPU_BIG1_1), U1.M16 (VDD_CPU_BIG0_0), U1.M17 (VDD_CPU_BIG0_9), U1.M23 (VDD_CPU_BIG1_7), U1.M24 (VDD_CPU_BIG1_2), U1.N16 (VDD_CPU_BIG0_1), U1.N17 (VDD_CPU_BIG0_8), U1.N23 (VDD_CPU_BIG1_6), U1.N24 (VDD_CPU_BIG1_3), U1.P16 (VDD_CPU_BIG0_2), U1.P17 (VDD_CPU_BIG0_7), U1.P23 (VDD_CPU_BIG1_5), U1.P24 (VDD_CPU_BIG1_4), U1.R16 (VDD_CPU_BIG0_3), U1.R17 (VDD_CPU_BIG0_6), U1.T16 (VDD_CPU_BIG0_4), U1.T17 (VDD_CPU_BIG0_5), U47.2, U48.2, U49.2, U50.2, U51.2, U54.A4 (VOUT)
VDD_CPU_LIT_S0: C53.2, C54.2, C55.2, C56.2, C73.2, C77.2, C78.2, C120.1, C121.2, C156.1, C156.2, C157.2, C158.2, C159.2, C160.2, L5.2, R44.1, R44.2, U1.T21 (VDD_CPU_LIT_MEM_1), U1.T22 (VDD_CPU_LIT_MEM_0), U1.U21 (VDD_CPU_LIT_7), U1.U22 (VDD_CPU_LIT_0), U1.V21 (VDD_CPU_LIT_6), U1.V22 (VDD_CPU_LIT_1), U1.W21 (VDD_CPU_LIT_5), U1.W22 (VDD_CPU_LIT_2), U1.Y21 (VDD_CPU_LIT_4), U1.Y22 (VDD_CPU_LIT_3), U18.37 (VOUT2)
VDD_DDR_S0: C1.2, C43.2, C57.2, C58.2, C193.2, C194.2, C195.2, C196.1, C196.2, C281.2, L12.2, R55.1, R55.2, U1.L11 (DDR_CH1_VDD_0), U1.L12 (DDR_CH1_VDD_1), U1.L13 (DDR_CH1_VDD_2), U1.L14 (DDR_CH1_VDD_3), U1.L17 (DDR_CH1_VDD_MIF_0), U1.L18 (DDR_CH1_VDD_MIF_1), U1.N13 (DDR_CH0_VDD_MIF_0), U1.P12 (DDR_CH0_VDD_3), U1.P13 (DDR_CH0_VDD_MIF_1), U1.R12 (DDR_CH0_VDD_2), U1.T12 (DDR_CH0_VDD_1), U1.U11 (DDR_CH0_VDD_0), U18.46 (VOUT5)
VDD_GPU_S0: C68.2, C69.2, C70.2, C71.2, C72.2, C79.2, C80.2, C81.2, C82.2, C150.1, C150.2, C151.2, C152.2, C153.2, C154.2, L3.2, R43.1, R43.2, U1.AA12 (VDD_GPU_MEM_0), U1.AA13 (VDD_GPU_0), U1.AA14 (VDD_GPU_7), U1.AA15 (VDD_GPU_11), U1.AB12 (VDD_GPU_MEM_1), U1.AB13 (VDD_GPU_1), U1.AB14 (VDD_GPU_6), U1.AB15 (VDD_GPU_10), U1.AC13 (VDD_GPU_2), U1.AC14 (VDD_GPU_5), U1.AC15 (VDD_GPU_9), U1.AD13 (VDD_GPU_3), U1.AD14 (VDD_GPU_4), U1.AD15 (VDD_GPU_8), U18.49 (VOUT1)
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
